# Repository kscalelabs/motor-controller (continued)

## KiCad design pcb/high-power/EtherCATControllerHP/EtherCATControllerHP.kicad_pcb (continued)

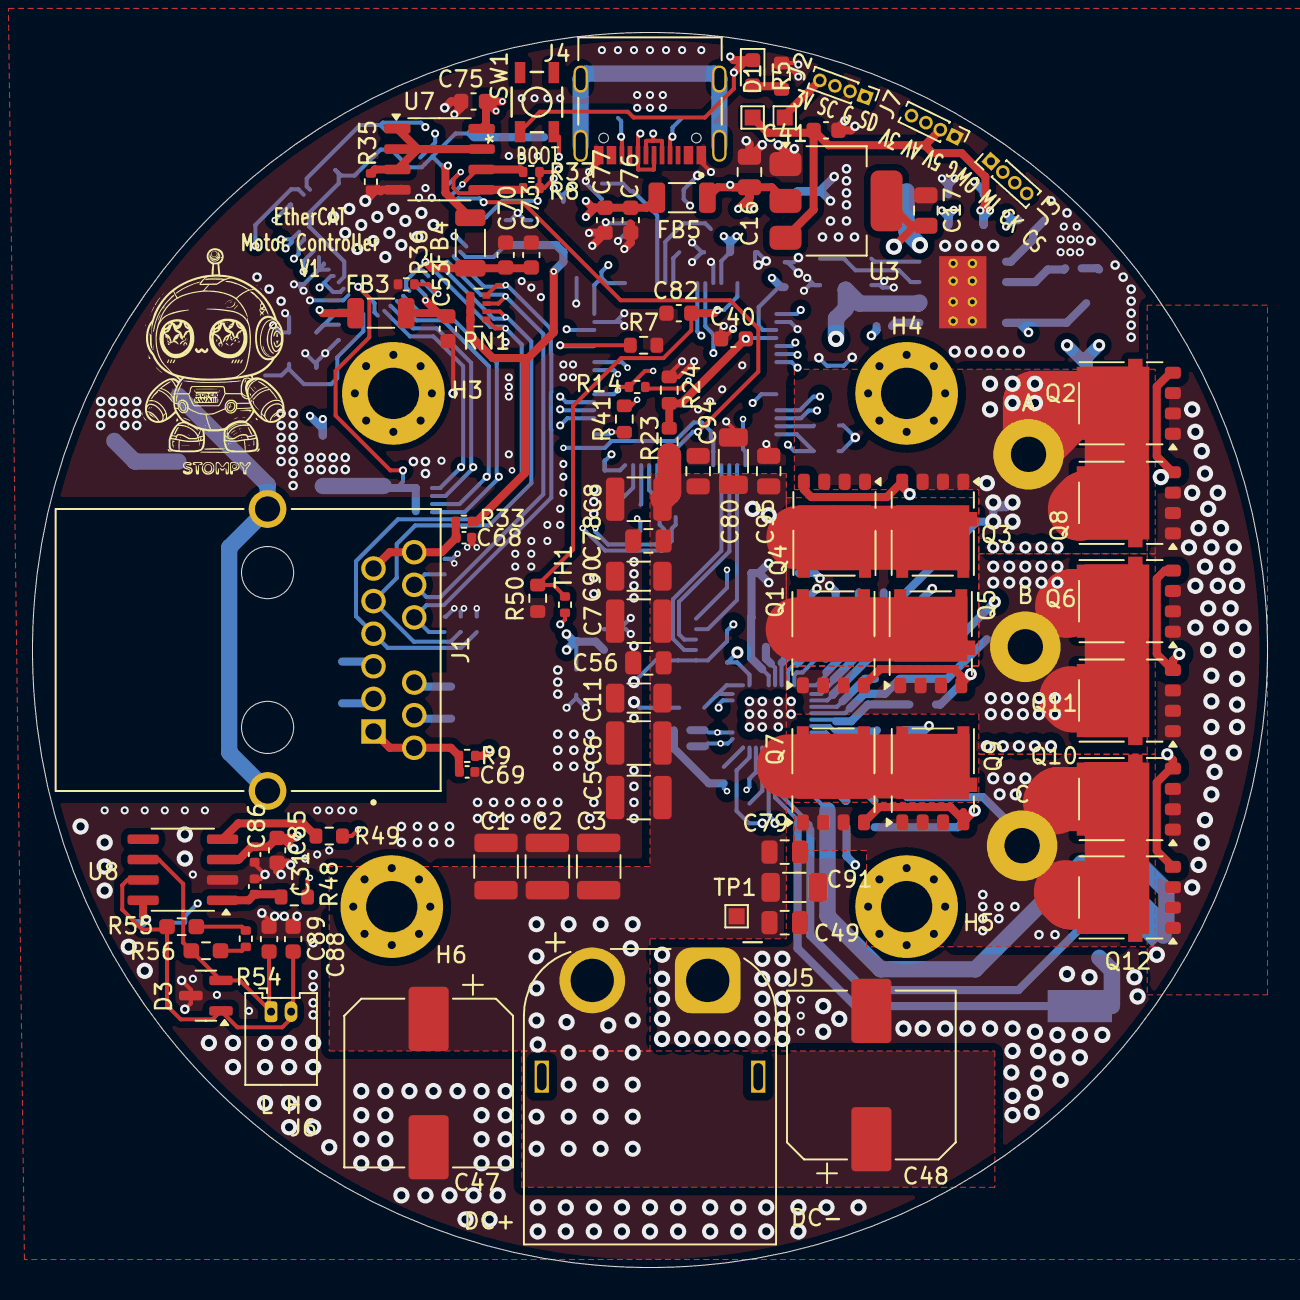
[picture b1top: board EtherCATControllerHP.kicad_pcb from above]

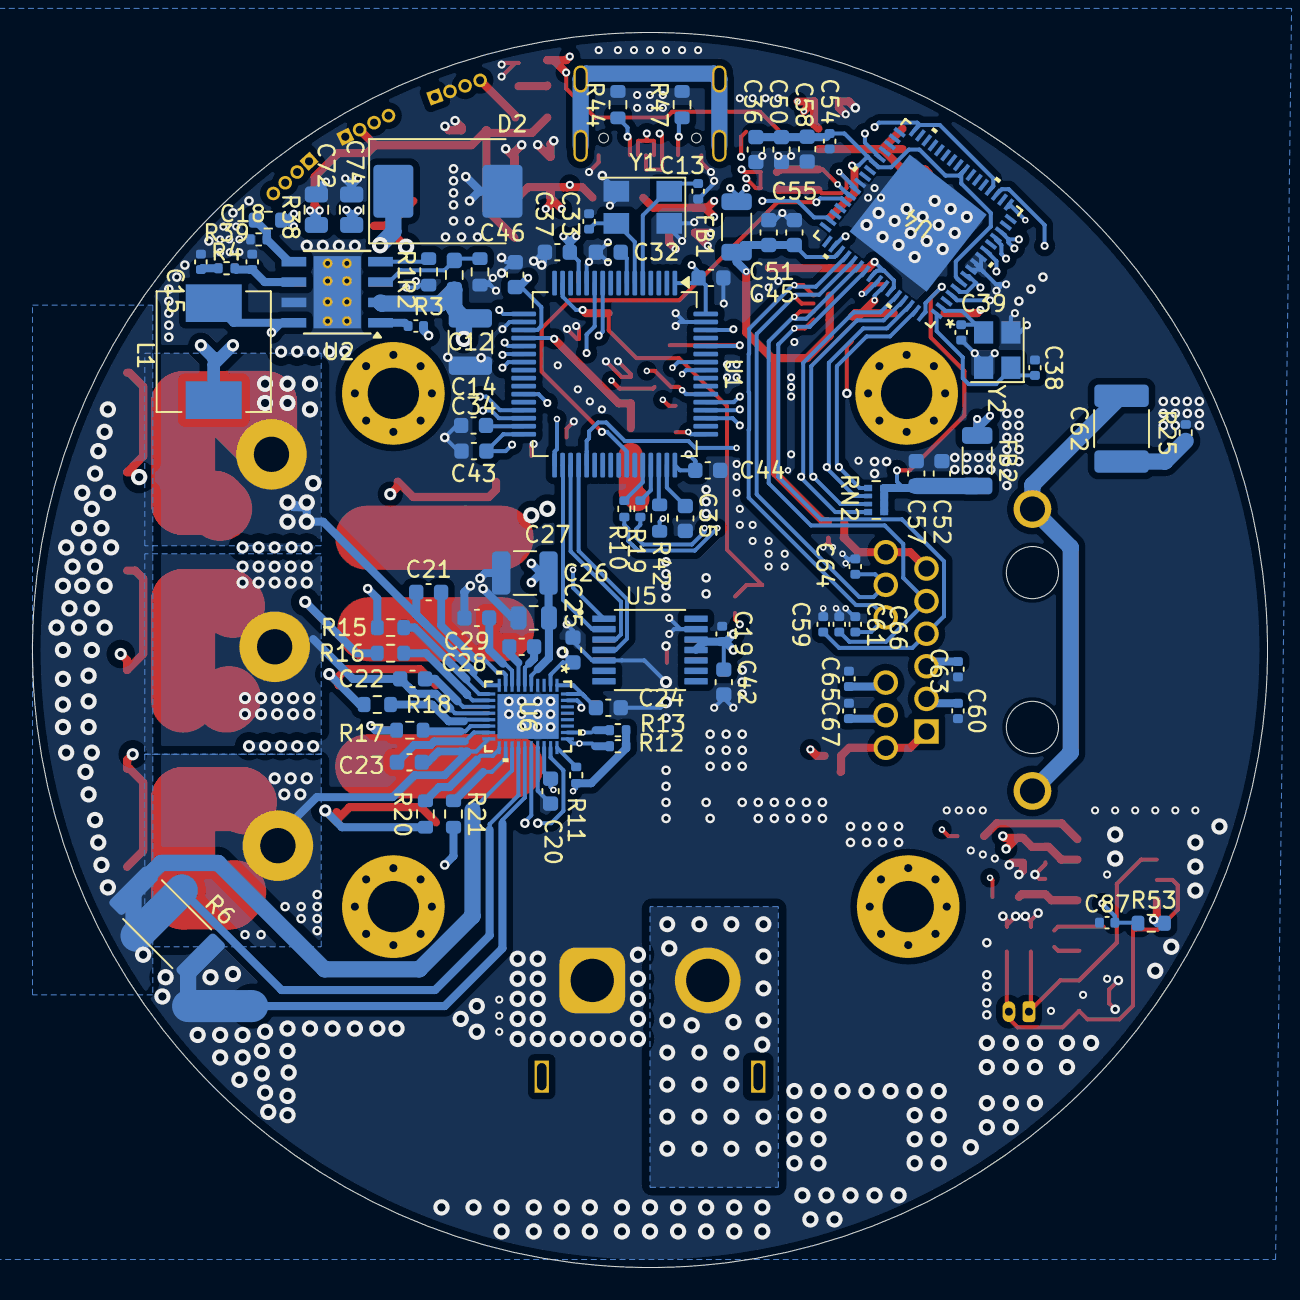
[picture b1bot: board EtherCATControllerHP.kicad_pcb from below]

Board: 6 copper layers, 77.0 x 77.0 mm, 180 parts (85 on the bottom side), 110 nets.

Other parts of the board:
A: SH_A; MountingHole_2.2mm_M2_Pad
B: SH_B; MountingHole_2.2mm_M2_Pad
C: SH_C; MountingHole_2.2mm_M2_Pad
C47: 100uF, 80V; CP_Elec_10x10

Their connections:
/SH_A: A.1; also elsewhere on the board
/SH_B: B.1; also elsewhere on the board
/SH_C: C.1; also elsewhere on the board
DCBUS: C47.1; also elsewhere on the board
GND: C47.2; also elsewhere on the board

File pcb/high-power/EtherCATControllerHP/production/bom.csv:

Designator,Footprint,Quantity,Value,LCSC Part #
"C1, C2, C27, C3, C5, C6, C7, C8",1210,8,10uF, C5156756
"C11, C80, C90, C91",1206,4,1uF,C13832
C12,1210,1,4.7uF,C6120033
"C13, C33, C59, C60, C61, C63, C64, C65, C66, C67",0402,10,10pF,C115606
C14,0402,1,0.1uF, C105883
C15,0402,1,6800pF,C93654
"C16, C17",0805,2,4.7uF,C913498
C18,0402,1,39pF,C147447
C19,0402,1,0.1uF,C77055
"C20, C24, C25, C36, C85",0603,5,1uF,C106858
"C21, C22, C23",0603,3,1uF,C105174
"C26, C49, C56, C78, C79, C94, C95",0805,7,0.1uF,C28233
C28,0603,1,470pF, C107062
C29,0603,1,10uF,C194427
"C31, C86, C87",0402,3,330pF,C526998
"C32, C37, C43, C44, C45, C46, C50, C53, C55, C57, C58, C70, C73, C75, C77, C88, C89",0603,17,0.1uF,C77055
"C34, C35",0603,2,2.2µF,C77183
"C38, C39",0402,2,18pF,C76701
"C40, C41, C82",0603,3,2.2uF,C77183
C42,0603,1,0.1uF,C14663
"C47, C48",CP_Elec_10x10,2,"100uF, 80V", C487410
"C51, C52, C76",0603,3,1uF, C106858
C54,0402,1,470pF,C106207
C62,1812,1,10nF, C574051
"C68, C69",0402,2,0.022uF,C147616
"C72, C74",0805,2,47uF,C178332
D1,0603,1,LTST-C190KGKT,C125094
D2,D_SMC,1,B560C,C85100
D3,SOT-23,1,SM24CANB-02HTG,C2937019
"FB1, FB2, FB3, FB4, FB5",1206,5,"2A, 0.05DCR",C380287
J4,HRO_TYPE-C-31-M-12,1,TYPE-C-31-M-12,C165948
J5,AMASS_XT60PW-M_1x02_P7.20mm_Horizontal,1,XT60PW-M,C98732
J6,Molex_PicoBlade_53048-0210_1x02_P1.25mm_Horizontal,1,2 pin Molex Picoblade,C505099
L1,L_Sunlord_MWSA0603S,1,8.2uH,C408450
"Q1, Q10, Q11, Q12, Q2, Q3, Q4, Q5, Q6, Q7, Q8, Q9",ONSemi_SO-8FL_488AA,12,~,C348543
R1,0603,1,162K, C227450
"R10, R19",0402,2,22R,C107701
"R11, R12, R13, R14",0402,4,5.1K, C105872
"R15, R16, R17, R18, R20, R21",0603,6,2.2R,C112307
R2,0603,1,523K,C23076
R23,0603,1,18K, C98220
"R24, R5",0603,2,1k,C22548
R25,0402,1,1M, C279988
R3,0603,1,84.5k,C706195
"R33, R9",0402,2,0,C106231
R35,0402,1,4.7k, C105871
R36,0402,1,12.1K, C281773
"R37, R8",0402,2,2k,C144035 
R38,0603,1,53.6K,C177851
R39,0402,1,10.2K,C321256
R4,0402,1,13K,C310197
"R41, R42, R48, R49, R53",0603,5,22R,C107701
"R44, R47",0603,2,5.1k, C706184
R50,0603,1,3.3k, C108078
R54,0402,1,120R,C114640
R6,2512,1,500uOhm,C500733 
R7,0603,1,47K,C105579
"RN1, RN2",R_Array_Convex_4x0402,2,49R9, C136850
SW1,SW_EVP-AA102K_PAN,1,EVP-AA202K,C79147
TH1,0402,1,10k,C77131
U1,LQFP-64_10x10mm_P0.5mm,1,STM32F405RGT6,C15742
U2,TI_SO-PowerPAD-8_ThermalVias,1,TPS54360DDAR,C524806
U3,SOT-223,1,LDL1117S33R,C435835
U4,QFN64_ML_MCH,1,LAN9252I/ML,C2758355
U5,SOP65P640X120-14N,1,AS5047P-ATSM,C962063
U6,WQFN36_REE_TEX,1,MCF8329A1IREER,C22399784
U7,SOP-8_3.9x4.9mm_P1.27mm,1,24FC512-I/SN,C615159
U8,SOIC-8_3.9x4.9mm_P1.27mm,1,SN65HVD231,C129257
Y1,Crystal_SMD_5032-4Pin_5.0x3.2mm,1,ABM3B-8.000MHZ-10-1-U-T, C276420
Y2,Crystal_SMD_3225-4Pin_3.2x2.5mm,1,ABM8-25.000MHZ-D2Y-T,C179643

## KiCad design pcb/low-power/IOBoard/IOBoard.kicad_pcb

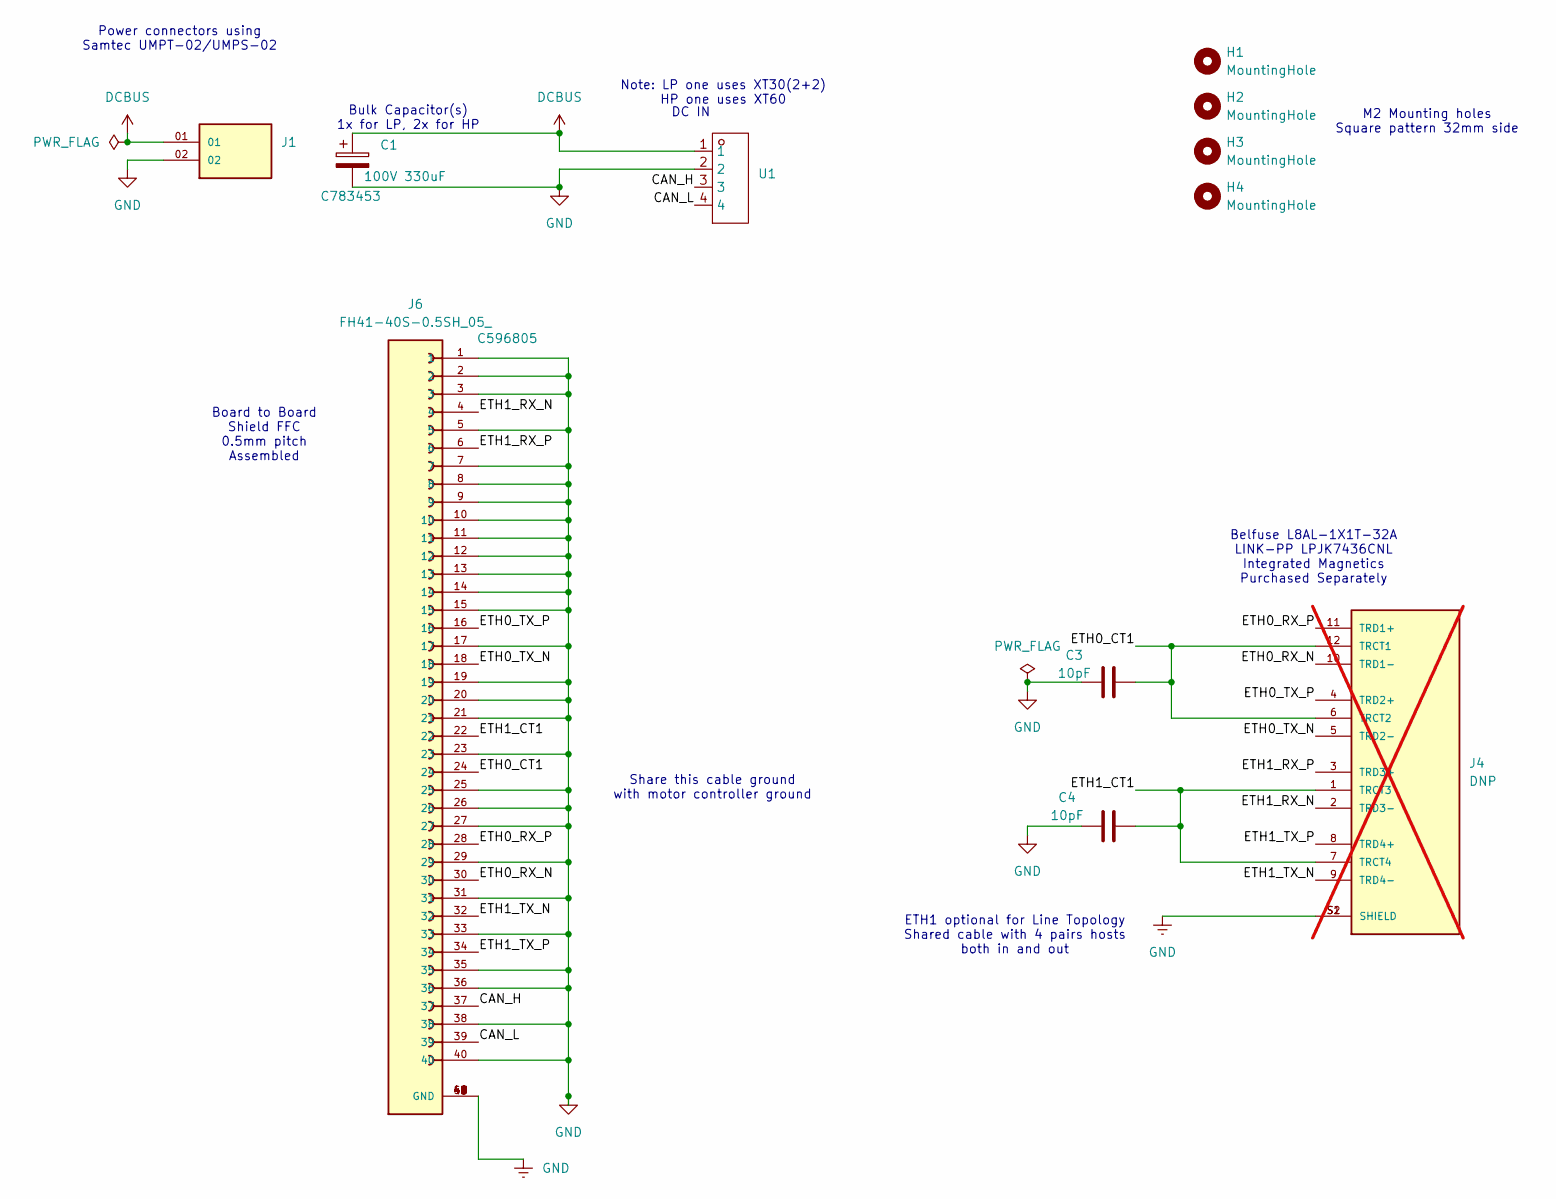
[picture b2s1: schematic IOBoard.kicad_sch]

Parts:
C1: 100V 330uF; CP_Radial_D13.0mm_P5.00mm-Horizontal; LCSC Part # C783453
C3, C4: 10pF; C_0402_1005Metric; LCSC Part # C650948
H1, H2, H3, H4: MountingHole; MountingHole_2.2mm_M2
J1: UMPS-02-03.5-G-V-S-W-TR; SAMTEC_UMPS-02-03.5-G-V-S-W-TR; PARTREV F
J4: DNP; BEL_L8AL-1X1T-32A; PARTREV A; not fitted
J6: FH41-40S-0.5SH_05_; HRS_FH41-40S-0.5SH_05_; PARTREV 18.03.19; LCSC Part # C596805
U1: CONN-TH_4P-XT30PW-M; Manufacturer Part XT30(2+2)PW-M.G.B; LCSC Part Name XT30PW(2+2)功率数据混合插头公金黑PCB弯插

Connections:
/CAN_H: J6.37, U1.3
/CAN_L: J6.39, U1.4
/ETH0_CT1: C3.2, J4.6 (TRCT2), J4.12 (TRCT1), J6.24
/ETH0_RX_N: J4.10 (TRD1-), J6.30
/ETH0_RX_P: J4.11 (TRD1+), J6.28
/ETH0_TX_N: J4.5 (TRD2-), J6.18
/ETH0_TX_P: J4.4 (TRD2+), J6.16
/ETH1_CT1: C4.2, J4.1 (TRCT3), J4.7 (TRCT4), J6.22
/ETH1_RX_N: J4.2 (TRD3-), J6.4
/ETH1_RX_P: J4.3 (TRD3+), J6.6
/ETH1_TX_N: J4.9 (TRD4-), J6.32
/ETH1_TX_P: J4.8 (TRD4+), J6.34
DCBUS: C1.1, J1.01, U1.1
GND: C1.2, C3.1, C4.1, J1.02, J4.S1 (SHIELD), J4.S2 (SHIELD), J6.1, J6.2, J6.3, J6.5, J6.7, J6.8, J6.9, J6.10, J6.11, J6.12, J6.13, J6.14, J6.15, J6.17, J6.19, J6.20, J6.21, J6.23, J6.25, J6.26, J6.27, J6.29, J6.31, J6.33, J6.35, J6.36, J6.38, J6.40, J6.41 (GND), J6.42 (GND), J6.43 (GND), J6.44 (GND), J6.45 (GND), J6.46 (GND), J6.47 (GND), J6.48 (GND), J6.49 (GND), J6.50 (GND), U1.2

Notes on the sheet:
Belfuse L8AL-1X1T-32A LINK-PP LPJK7436CNL Integrated Magnetics Purchased Separately
ETH1 optional for Line Topology Shared cable with 4 pairs hosts both in and out
M2 Mounting holes Square pattern 32mm side
Board to Board Shield FFC 0.5mm pitch Assembled
Share this cable ground with motor controller ground
DC IN
Power connectors using Samtec UMPT-02/UMPS-02
Note: LP one uses XT30(2+2) HP one uses XT60
Bulk Capacitor(s) 1x for LP, 2x for HP

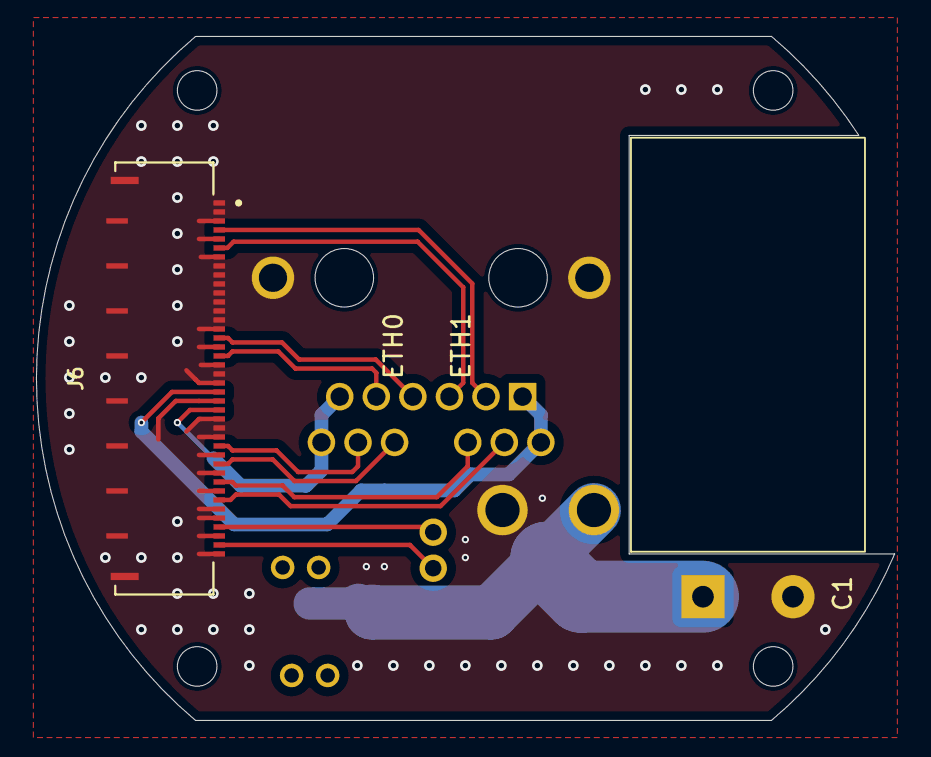
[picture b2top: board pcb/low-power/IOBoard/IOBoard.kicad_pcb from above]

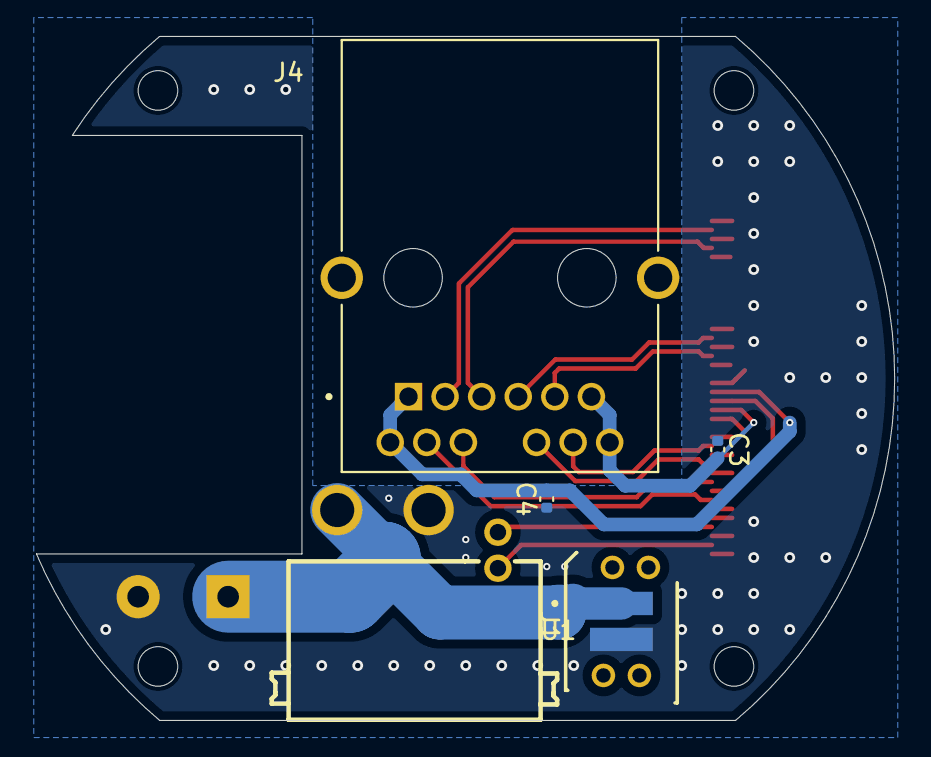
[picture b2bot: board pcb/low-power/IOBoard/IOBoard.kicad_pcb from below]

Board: 2 copper layers, 47.7 x 38.0 mm, 11 parts (5 on the bottom side), 14 nets.

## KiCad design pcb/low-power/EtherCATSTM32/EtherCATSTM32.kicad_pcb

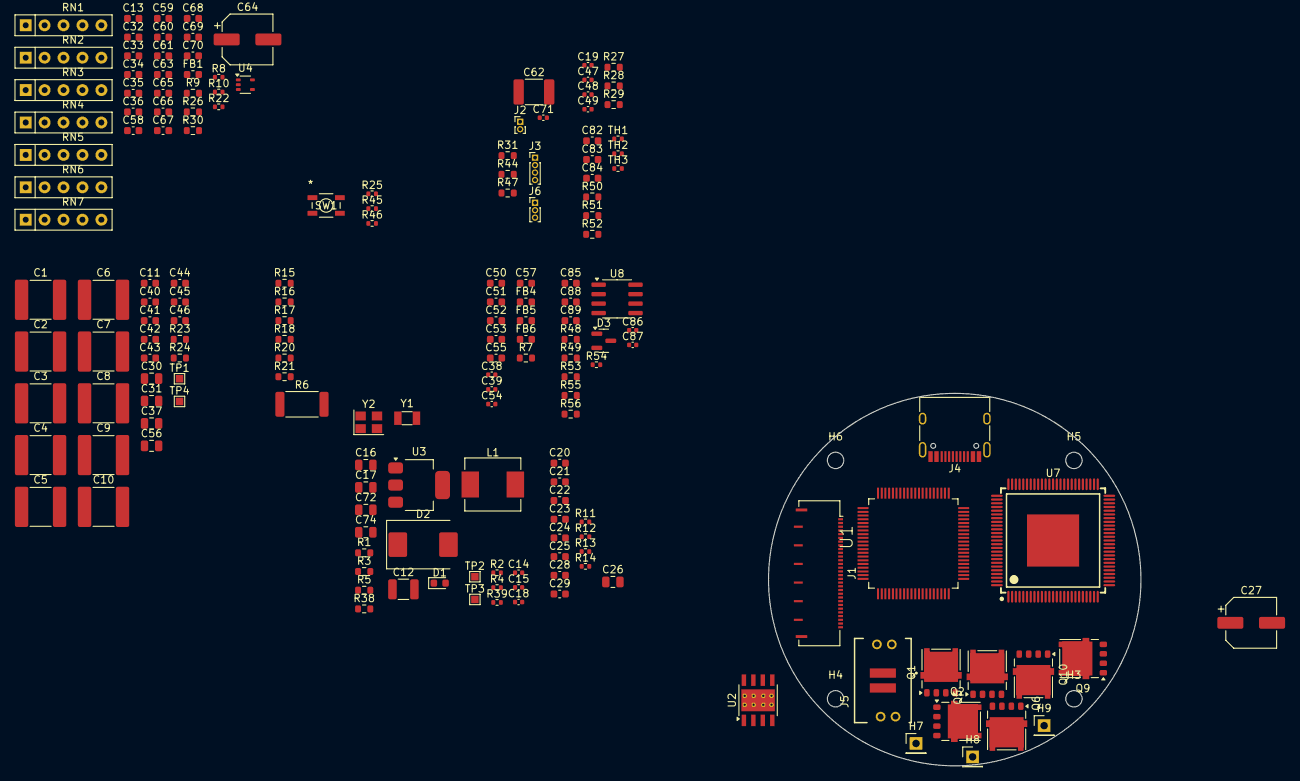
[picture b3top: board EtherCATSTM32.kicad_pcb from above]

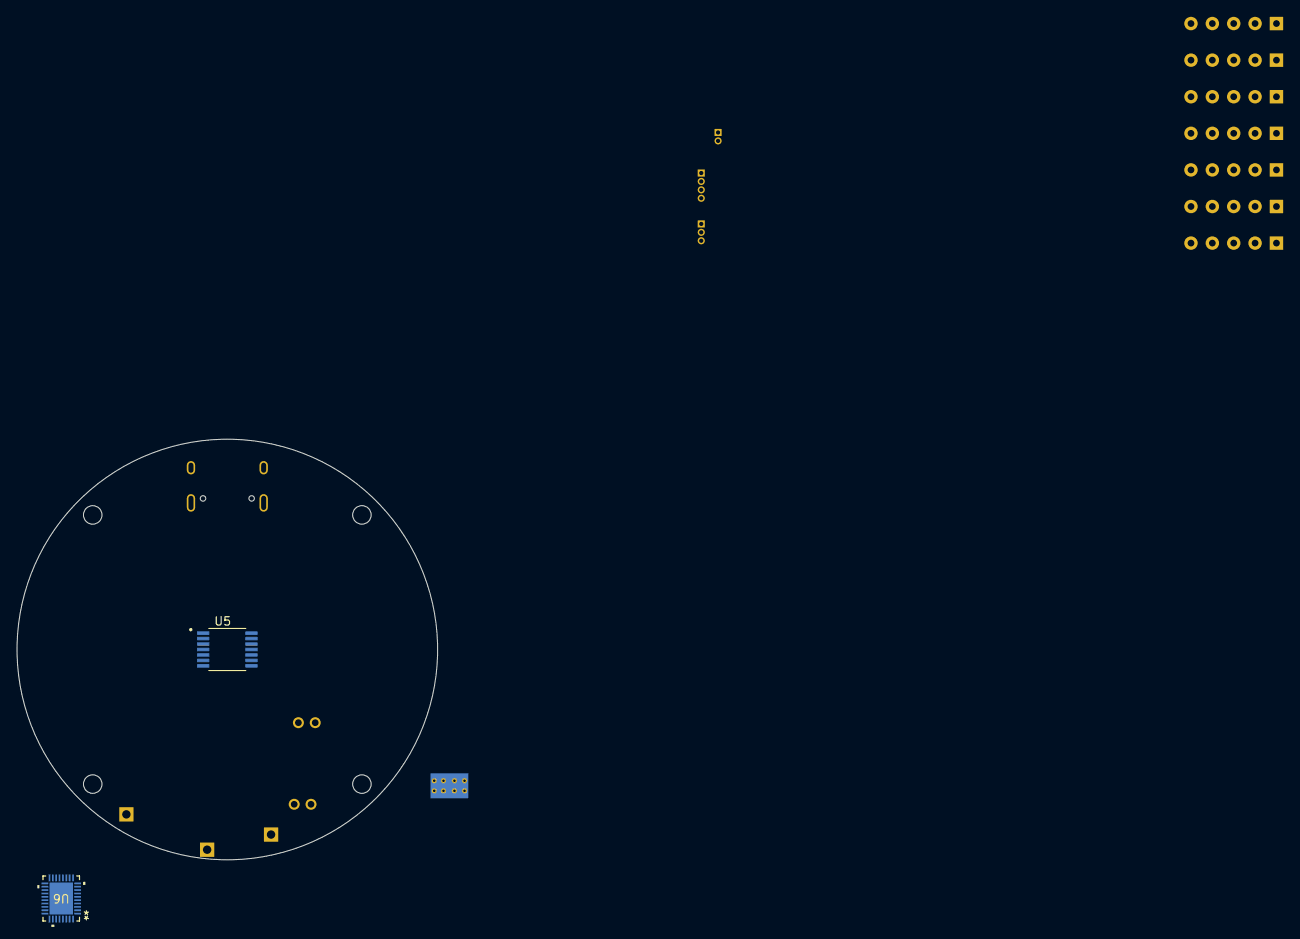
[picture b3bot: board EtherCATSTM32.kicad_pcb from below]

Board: 6 copper layers, 178 parts (2 on the bottom side), 144 nets, no tracks yet.

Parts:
C1, C2, C3, C4, C5, C6, C9, C10: 10uF; C_2220_5750Metric
C7, C8: 22uF; C_2220_5750Metric
C11, C13, C32, C33, C34, C35, C36, C42, C43, C44, C45, C46, C50, C51, C52, C53, C55, C57, C58, C59, C60, C61, C63, C65, C66, C67, C68, C69, C70, C88, C89: 0.1uF; C_0603_1608Metric
C12: 4.7uF; C_1210_3225Metric
C14, C19: 0.1uF; C_0402_1005Metric
C15: 6800pF; C_0402_1005Metric
C16, C17: 4.7uF; C_0805_2012Metric
C18: 39pF; C_0402_1005Metric
C20, C21, C22, C23, C24, C25, C85: 1uF; C_0603_1608Metric
C26: 0.1uF; C_0805_2012Metric
C27, C64: 10uF; CP_Elec_6.3x5.4
C28: 470pF; C_0603_1608Metric
C29: 10uF; C_0603_1608Metric
C30, C31, C37, C56: 10uF; C_0805_2012Metric
C38, C39: 15pF; C_0402_1005Metric
C40, C41, C82, C83, C84: 2.2uF; C_0603_1608Metric
C47, C48, C49: 22nF; C_0402_1005Metric
C54: 10uF; C_0402_1005Metric
C62: 10nF; C_1812_4532Metric
C71: 10nF; C_0402_1005Metric
C72, C74: 47uF; C_0805_2012Metric
C86, C87: 330pF; C_0402_1005Metric
D1: LTST-C190KGKT; D_0603_1608Metric
D2: B560C; D_SMC
D3: SM24CANB-02HTG; SOT-23
FB1, FB4, FB5, FB6: BLM18PG600; L_0603_1608Metric
H3, H4, H5, H6: MountingHole; MountingHole_2.2mm_M2
H7: SH_A; PinHeader_1x01_P2.54mm_Vertical
H8: SH_B; PinHeader_1x01_P2.54mm_Vertical
H9: SH_C; PinHeader_1x01_P2.54mm_Vertical
J1: FH41-40S-0.5SH_05_; Hirose_FH41-30S-0.5SH_1x30_1MP_1SH_P0.5mm_Horizontal
J2: Conn_01x02_Socket; PinHeader_1x02_P1.00mm_Vertical
J3: Conn_01x04_Socket; PinHeader_1x04_P1.00mm_Vertical
J4: TYPE-C-31-M-12; USB_C_Receptacle_HRO_TYPE-C-31-M-12
J5: Mounting holes; SAMTEC_UMPT-02-12.5-X-V-S-W-X
J6: Conn_01x03_Pin; PinHeader_1x03_P1.00mm_Vertical
L1: 8.2uH; L_Sunlord_MWSA0603S
Q1, Q2, Q5, Q6, Q9, Q10: ONSemi_SO-8FL_488AA
R1: 162K; R_0603_1608Metric
R2: 523K; R_0402_1005Metric
R3: 84R5; R_0603_1608Metric
R4: 13K; R_0402_1005Metric
R5, R24: 1k; R_0603_1608Metric
R6: 500uOhm; R_2512_6332Metric
R7: 510R; R_0603_1608Metric
R8: 1.5K; R_0402_1005Metric
R9: 4.87k, 1%; R_0603_1608Metric
R10, R22: 2.2K; R_0402_1005Metric
R11, R12, R13, R14: 5.1K; R_0402_1005Metric
R15, R16, R17, R18, R20, R21: 2.2R; R_0603_1608Metric
R23: 18K; R_0603_1608Metric
R25: 1M; R_0402_1005Metric
R26, R30, R31: 10k; R_0603_1608Metric
R27, R28, R29, R50, R51, R52: 3.3k; R_0603_1608Metric
R38: 53.6K; R_0603_1608Metric
R39: 10.2K; R_0402_1005Metric
R44, R47: 5.1k; R_0603_1608Metric
R45, R46: 22R; R_0402_1005Metric
R48, R49, R53: 22R; R_0603_1608Metric
R54: 120R; R_0402_1005Metric
R55, R56: 0; R_0603_1608Metric
RN1, RN2, RN3, RN4, RN5, RN6, RN7: 49R9; R_Array_SIP5
SW1: EVP-AA202K; SW_EVP-AA102K_PAN
TH1, TH2, TH3: 10k; R_0402_1005Metric
TP1, TP2, TP3, TP4: TESTPOINT; TestPoint_Pad_1.0x1.0mm
U1: DP83849IFVS_NOPB; QFP50P1400X1400X120-80N
U2: TPS54360DDAR; TI_SO-PowerPAD-8_ThermalVias
U3: LDL1117S33R; SOT-223
U4: NC7SZ125P5X; SOT-353_SC-70-5
U5: AS5047P-ATSM; SOP65P640X120-14N
U6: MCF8329A1IREER; WQFN36_REE_TEX
U7: LQFP-100-XMC4800
U8: SN65HVD231; SOIC-8_3.9x4.9mm_P1.27mm
Y1: 32.768 KHZ; Crystal_SMD_3215-2Pin_3.2x1.5mm
Y2: 12 MHz; Crystal_SMD_3225-4Pin_3.2x2.5mm

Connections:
5V: C41.1, C72.1, C74.1, L1.2, R38.1, TP3.1, U3.3 (VIN)
/BRAKE: U6.34 (BRAKE), U7.89 (P0.7)
/CAN_H: C88.1, D3.1 (A1), R55.1, U8.7 (CANH)
/CAN_L: C89.2, D3.2 (A2), R56.2, U8.6 (CANL)
/CAN_MODE: C87.2, R53.1, U7.69 (P1.14)
/CAN_RX: R49.1, U7.70 (P1.13)
/CAN_TX: R48.1, U7.71 (P1.12)
/DIR: U6.31 (DIR), U7.88 (P0.8)
/DRVOFF: U6.24 (DRVOFF), U7.72 (P1.11)
/ECAT0.P0_RXD3: RN3.5 (R4.2), U7.55 (P5.7)
/ECAT0.P0_RXDO: R10.2, U7.58 (P5.0)
/ECAT0.P0_TXD3: RN1.5 (R4.2), U7.77 (P1.2)
/ECAT0.P0_TX_ENA: U1.13 (TX_EN_A), U7.76 (P1.3)
/ECAT0.P1_RXD3: RN4.5 (R4.2), U7.21 (P14.14)
/ECAT0.P1_RX_DVA: U1.62 (RX_DV_B/MII_MODE_B), U7.20 (P14.15)
/ECAT0.P1_RX_ERRB: U1.60 (RX_ER_B/MDIX_EN_B), U7.19 (P15.2)
/ECAT0.P1_TXD1: RN2.5 (R4.2), U7.5 (P3.2)
/ECAT0.P1_TX_ENA: U1.49 (TX_EN_B), U7.7 (P3.0)
/ECAT0.PO_RX_DVA: U1.80 (RX_DV_A/MII_MODE_A), U7.80 (P1.9)
/ECAT0.PO__RX_CLK: RN5.5 (R4.2), U7.78 (P1.1)
/ECAT0_P0_RX_ERRB: U1.2 (RX_ER_A/MDIX_EN_A), U7.54 (P2.6)
/ECAT_RST: R26.1, U4.2 (A), U7.2 (P0.0)
/ETH0_CT1: C69.1, J1.24
/ETH0_RXN: J1.30, U1.23 (TPRDM_A)
/ETH0_RXP: J1.28, RN7.2 (R2.1), U1.24 (TPRDP_A)
/ETH0_TXN: J1.18, RN6.3 (R3.1), U1.26 (TPTDM_A), U1.36 (TPTDM_B)
/ETH0_TXP: J1.16, RN7.5 (R4.2), U1.27 (TPTDP_A)
/ETH1_CT1: C70.1, J1.22
/ETH1_RXN: J1.4, RN6.1 (R1.1), U1.39 (TPRDM_B)
/ETH1_RXP: J1.6, U1.38 (TPRDP_B)
/ETH1_TXP: RN6.4 (R4.1), U1.35 (TPTDP_B)
/ETH_PHY_CLK: U1.70 (X1), U7.85 (P4.0)
/Encoders/ENC_A: C47.1, R27.2
/Encoders/ENC_B: C48.1, R28.2
/Encoders/ENC_Z: C49.1, R29.2
/EtherCAT/COL_PHYAD0_A: R22.1, U1.3 (COL_A)
/EtherCAT/PFBOUT: C58.1, C59.1, C60.1, C61.1, C63.1, C64.1, U1.7 (PFBIN1), U1.28 (PFBIN2), U1.31 (PFBOUT), U1.34 (PFBIN3), U1.54 (PFBIN4)
/EtherCAT/PHY_RST: R30.1, U1.71 (RESET_N), U4.4 (Y)
/EtherCAT/VCCTXRX: C66.1, C67.1, C68.1, FB1.1, RN6.2 (R2.1), RN6.5 (R4.2), RN7.1 (R1.1), RN7.3 (R3.1), RN7.4 (R4.1)
/I2C_SCL: R13.2, U6.30 (SCL), U7.48 (P2.4)
/I2C_SDA: R12.2, U6.29 (SDA), U7.47 (P2.5)
/MCU/RTC_XTAL1: C39.1, U7.16 (RTC_XTAL1), Y1.2
/MCU/RTC_XTAL2: C38.1, U7.15 (RTC_XTAL2), Y1.1
/MCU/VAREF: C57.1, FB5.1, U7.33 (VAREF)
/MCU/VDDA: C55.1, FB6.1, U7.35 (VDDA)
/MCU/XTAL1: U7.61 (XTAL1), Y2.1
/MCU/XTAL2: R7.2, U7.62 (XTAL2)
/MDC: U1.67 (MDC), U7.93 (P3.3)
/MDIO: R8.2, U1.66 (MDIO), U7.94 (P0.12)
/Motor/DVDD: C24.2, U6.1 (DGND), U6.36 (DVDD)
/Motor/GH_A: R15.2, U6.11 (GHA)
/Motor/GH_B: R18.2, U6.15 (GHB)
/Motor/GH_C: R20.2, U6.19 (GHC)
/Motor/GL_A: R16.1, U6.12 (GLA)
/Motor/GL_B: R17.2, U6.16 (GLB)
/Motor/GL_C: R21.1, U6.20 (GLC)
/Motor/SENSE_P: Q2.1 (S), Q2.2 (S), Q2.3 (S), Q6.1 (S), Q6.2 (S), Q6.3 (S), Q10.1 (S), Q10.2 (S), Q10.3 (S), R6.1, U6.21 (LSS), U6.22 (SP)
/NFAULT: R14.2, U6.35 (NFAULT), U7.30 (P14.1)
/POWERDOWN_A: U1.18 (PWRDOWN_INT_A), U7.46 (P2.8)
/POWERDOWN_B: U1.44 (PWRDOWN_INT_B), U7.45 (P2.9)
/Power/Regulators/FB: R38.2, R39.1, U2.5 (FB)
/RESET: C71.1, R31.2, SW1.1, U7.65 (PORST#)
/SH_A: C21.1, H7.1, Q1.1 (S), Q1.2 (S), Q1.3 (S), Q2.5 (D), U6.10 (SHA)
/SH_B: C22.1, H9.1, Q5.1 (S), Q5.2 (S), Q5.3 (S), Q6.5 (D), U6.14 (SHB)
/SH_C: C23.1, H8.1, Q9.1 (S), Q9.2 (S), Q9.3 (S), Q10.5 (D), U6.18 (SHC)
/SPI1_CS: U5.1 (CSN), U7.84 (P4.1)
/SPI1_MISO: U5.3 (MISO), U7.92 (P3.4)
/SPI1_MOSI: U5.4 (MOSI), U7.91 (P3.5)
/SPI1_SCK: U5.2 (CLK), U7.90 (P3.6)
/SPI_CS: J3.1, U7.96 (P0.6)
/SPI_MISO: J3.3, U7.98 (P0.4)
/SPI_MOSI: J3.4, U7.97 (P0.5)
/SPI_SCK: J3.2, U7.95 (P0.11)
/SWV: J6.3, U7.51 (P2.1)
/TCK: J6.2, U7.67 (TCK)
/TEMP_BACKSIDE: C84.1, R52.1, TH3.2, U7.28 (P14.3)
/TEMP_ICS: C83.1, R51.1, TH2.2, U7.27 (P14.4)
/TEMP_MOSFETS: C82.1, R50.1, TH1.2, U7.29 (P14.2)
/TMS: J6.1, U7.66 (TMS)
/UART_RX: J2.2, U7.40 (P2.15)
/UART_TX: J2.1, U7.41 (P2.14)
/USB_D+: J4.A6 (DP1), R46.2, U7.9 (USB_DP)
/USB_D-: J4.A7 (DN1), R45.2, U7.8 (USB_DM)
/VBUS_SENSE: C40.1, R23.2, R24.1, TP4.1, U7.31 (P14.0)
/WAKE: U6.27 (SPEED/_WAKE), U7.73 (P1.10)
AVCC: C19.1, C20.1, C25.2, C42.1, R11.1, R12.1, R13.1, R14.1, R27.1, R28.1, R29.1, TH1.1, TH2.1, TH3.1, U5.11 (VDD), U5.12 (VDD3V3), U6.2 (VREG), U6.26 (AVDD)
DCBUS: C1.1, C2.1, C3.1, C4.1, C5.1, C6.1, C7.1, C8.1, C9.1, C10.1, C12.1, C26.1, C27.1, Q1.5 (D), Q5.5 (D), Q9.5 (D), R2.1, R23.1, TP1.1, U2.2 (VIN), U6.5 (PVDD)
GND: C1.2, C2.2, C3.2, C4.2, C5.2, C6.2, C7.2, C8.2, C9.2, C10.2, C11.2, C12.2, C13.2, C15.2, C16.2, C17.2, C18.2, C19.2, C20.2, C24.1, C25.1, C26.2, C27.2, C29.1, C30.2, C31.2, C32.2, C33.2, C34.2, C35.2, C36.2, C37.2, C38.2, C39.2, C40.2, C41.2, C42.2, C43.2, C44.2, C45.2, C46.2, C47.2, C48.2, C49.2, C50.2, C51.2, C52.2, C53.2, C54.2, C55.2, C56.2, C57.2, C58.2, C59.2, C60.2, C61.2, C63.2, C64.2, C65.2, C66.2, C67.2, C68.2, C69.2, C70.2, C71.2, C72.2, C74.2, C82.2, C83.2, C84.2, C85.1, C86.1, C87.1, C88.2, C89.1, D2.2 (A), D3.3 (common), J1.1, J1.2, J1.3, J1.5, J1.7, J1.8, J1.9, J1.10, J1.11, J1.12, J1.13, J1.14, J1.15, J1.17, J1.19, J1.20, J1.21, J1.23, J1.25, J1.26, J1.27, J1.29, R1.2, R3.2, R5.2, R6.2, R9.1, R22.2, R24.2, R25.2, R26.2, R30.2, R39.2, R44.2, R47.2, R50.2, R51.2, R52.2, SW1.3, U1.6 (COREGND1), U1.10 (IOGND1), U1.22 (ANAGND1), U1.25 (CDGND1), U1.29 (ANAGND2), U1.33 (ANAGND3), U1.37 (CDGND2), U1.40 (ANAGND4), U1.52 (IOGND2), U1.55 (COREGND2), U1.64 (IOGND3), U1.77 (IOGND4), U2.3 (EN), U2.7 (GND), U2.9 (GNDPAD), U3.1 (GND), U4.1 (~OE), U4.3 (GND), U5.5 (TEST), U5.13 (GND), U6.4 (GND), U6.23 (SN), U6.25 (AGND), U6.37 (epad), U7.32 (VAGND), U7.34 (VSSA), U7.59 (VSS), U7.63 (VSSO), U7.101 (EP), U8.2 (GND), Y2.2, Y2.4
unnamed: C15.1, R4.2
unnamed: C62.1, R25.1
unnamed: D1.2, R5.1, TP2.1
unnamed: C14.2, D2.1 (K), L1.1, U2.8 (SW)
unnamed: J4.A5 (CC1), R44.1
unnamed: J4.B5 (CC2), R47.1
unnamed: J4.B7 (DN2), R45.1
unnamed: J4.B6 (DP2), R46.1
unnamed: Q1.4 (G), R15.1
unnamed: Q2.4 (G), R16.2
unnamed: Q5.4 (G), R18.1
unnamed: Q6.4 (G), R17.1
unnamed: Q9.4 (G), R20.1
unnamed: Q10.4 (G), R21.2
unnamed: R2.2, R3.1
unnamed: R7.1, Y2.3
unnamed: R54.1, R56.1
unnamed: R54.2, R55.2
unnamed: RN1.1 (R1.1), U1.14 (TXD0_A)
unnamed: RN1.2 (R2.1), U1.15 (TXD1_A)
unnamed: RN1.3 (R3.1), U1.16 (TXD2_A)
unnamed: RN1.4 (R4.1), U1.17 (TXD3_A/SNI_MODE_A)
unnamed: RN2.1 (R1.1), U1.45 (TXD3_B/SNI_MODE_B)
unnamed: RN2.2 (R2.1), U1.46 (TXD2_B)
unnamed: RN2.3 (R3.1), U1.48 (TXD0_B)
unnamed: RN2.4 (R4.1), U1.47 (TXD1_B)
unnamed: RN3.1 (R1.1), U1.4 (RXD0_A/PHYAD1)
unnamed: RN3.2 (R2.1), U1.5 (RXD1_A/PHYAD2)
unnamed: RN3.3 (R3.1), U1.8 (RXD2_A/CLK2MAC_DIS)
unnamed: RN3.4 (R4.1), U1.9 (RXD3_A/ED_EN_A)
unnamed: RN4.1 (R1.1), U1.58 (RXD0_B/PHYAD3)
unnamed: RN4.2 (R2.1), U1.57 (RXD1_B/PHYAD4)
unnamed: RN4.3 (R3.1), U1.56 (RXD2_B)
unnamed: RN4.4 (R4.1), U1.53 (RXD3_B/ED_EN_B)
unnamed: RN5.1 (R1.1), U1.12 (TX_CLK_A)
unnamed: RN5.2 (R2.1), U1.50 (TX_CLK_B)
unnamed: RN5.3 (R3.1), U1.63 (RX_CLK_B)
unnamed: RN5.4 (R4.1), U1.79 (RX_CLK_A)
unnamed: R9.2, U1.32 (RBIAS)
unnamed: C14.1, U2.1 (BOOT)
unnamed: C18.1, R4.1, U2.6 (COMP)
unnamed: R1.1, U2.4 (RT/CLK)
unnamed: C21.2, U6.9 (BSTA)
unnamed: C22.2, U6.13 (BSTB)
unnamed: C23.2, U6.17 (BSTC)
unnamed: C28.2, U6.7 (CPH)
unnamed: C28.1, U6.6 (CPL)
unnamed: R11.2, U6.28 (FG)
unnamed: C29.2, U6.8 (GVDD)
unnamed: FB4.2, U7.10 (VBUS)
unnamed: R48.2, U8.1 (D)
unnamed: R49.2, U8.4 (R)
unnamed: R53.2, U8.8 (Rs)
SHIELD: C62.2, J4.S1 (SHIELD)
VCC: C11.1, C13.1, C16.1, C17.1, C30.1, C31.1, C32.1, C33.1, C34.1, C35.1, C36.1, C37.1, C43.1, C44.1, C45.1, C46.1, C56.1, C65.1, C85.2, C86.2, D1.1, FB1.2, FB5.2, FB6.2, R8.1, R10.1, R31.1, U1.11 (IOVDD1), U1.30 (ANA33VDD), U1.51 (IOVDD2), U1.65 (IOVDD3), U1.78 (IOVDD4), U3.2 (VOUT), U3.4 (VOUT), U4.5 (VCC), U7.11 (VDDP), U7.12 (VDDC), U7.17 (VBAT), U7.43 (VDDP), U7.60 (VDDP), U7.87 (VDDP), U8.3 (VCC)
VDDC: C50.1, C51.1, C52.1, C53.1, C54.1, U7.42 (VDDC), U7.64 (VDDC), U7.86 (VDDC)

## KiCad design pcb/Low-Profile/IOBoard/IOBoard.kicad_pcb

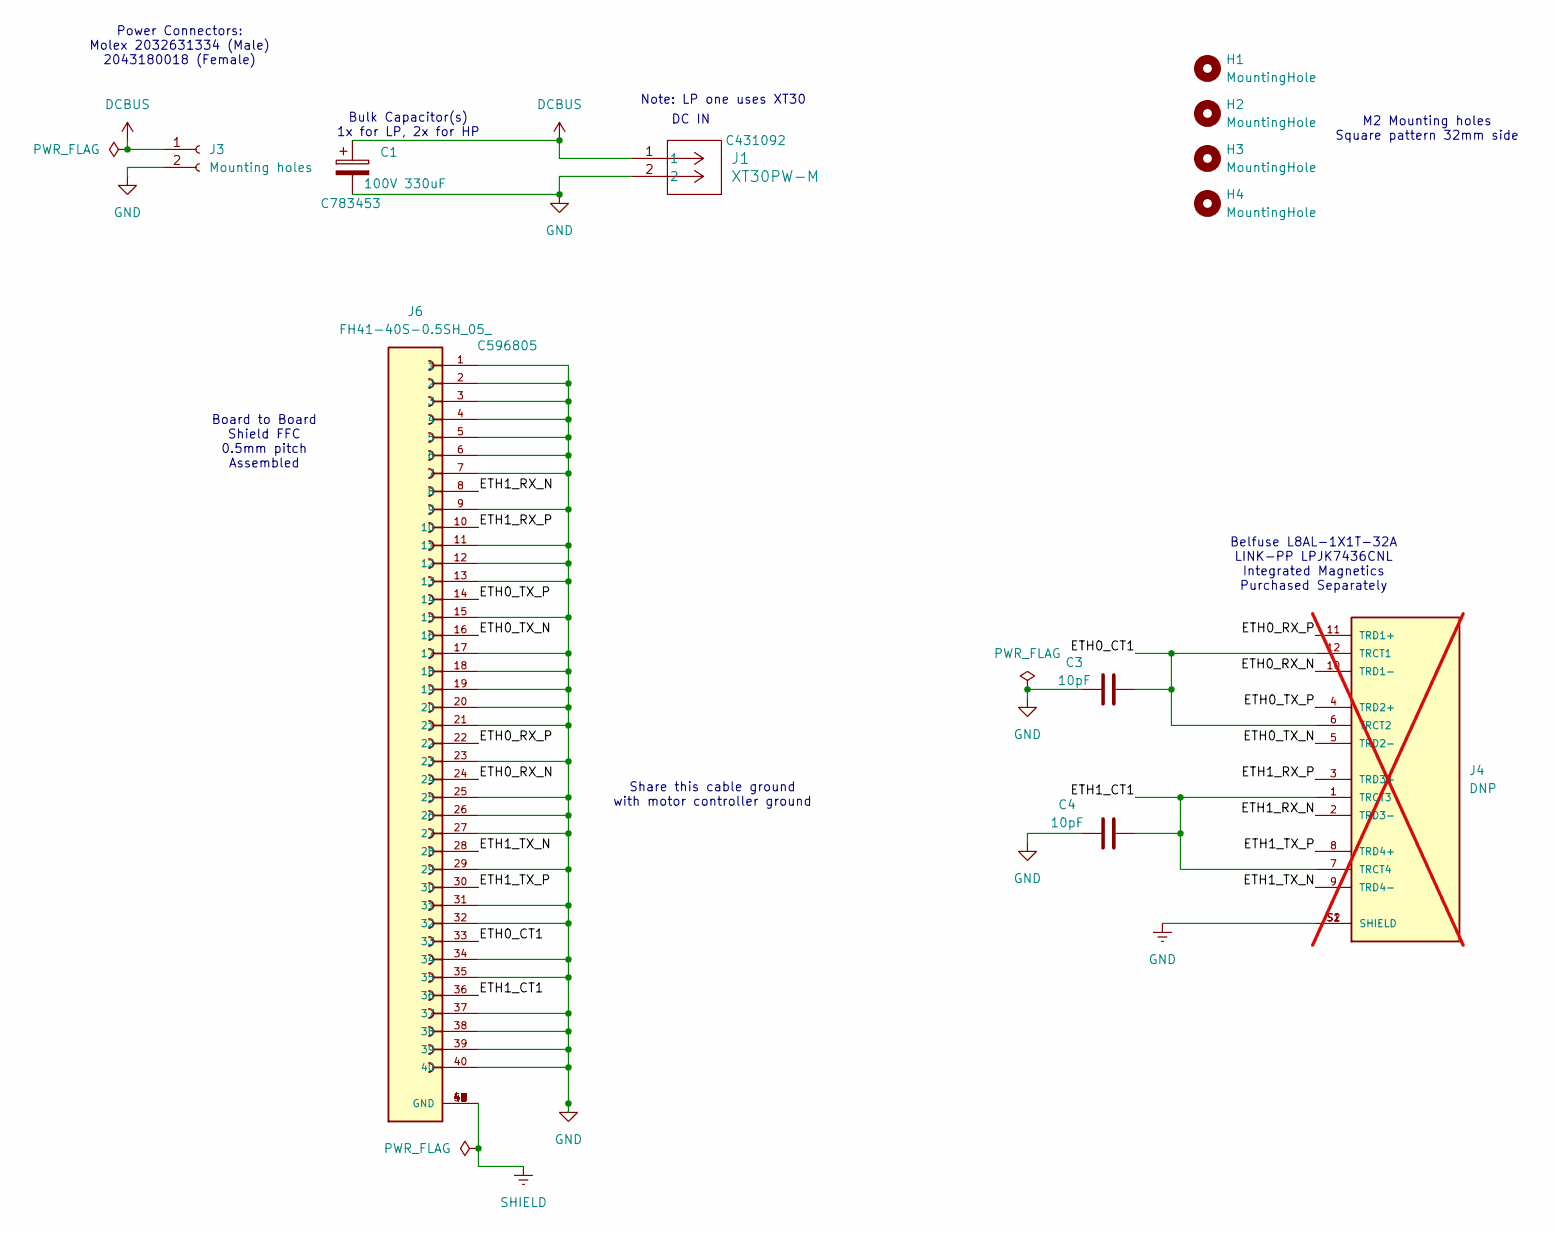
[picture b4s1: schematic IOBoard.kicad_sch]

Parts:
C1: 100V 330uF; CP_Radial_D13.0mm_P5.00mm-Horizontal; LCSC Part # C783453
C3, C4: 10pF; C_0402_1005Metric; LCSC Part # C650948
H1, H2, H3, H4: MountingHole; MountingHole_2.2mm_M2
J1: XT30PW-M; AMASS_XT30PW-M_1x02_P2.50mm_Horizontal; LCSC Part # C431092
J3: Mounting holes; Dual Post
J4: DNP; BEL_L8AL-1X1T-32A; PARTREV A; not fitted
J6: FH41-40S-0.5SH_05_; HRS_FH41-40S-0.5SH_05_; PARTREV 18.03.19; LCSC Part # C596805

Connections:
/ETH0_CT1: C3.2, J4.6 (TRCT2), J4.12 (TRCT1), J6.33
/ETH0_RX_N: J4.10 (TRD1-), J6.24
/ETH0_RX_P: J4.11 (TRD1+), J6.22
/ETH0_TX_N: J4.5 (TRD2-), J6.16
/ETH0_TX_P: J4.4 (TRD2+), J6.14
/ETH1_CT1: C4.2, J4.1 (TRCT3), J4.7 (TRCT4), J6.36
/ETH1_RX_N: J4.2 (TRD3-), J6.8
/ETH1_RX_P: J4.3 (TRD3+), J6.10
/ETH1_TX_N: J4.9 (TRD4-), J6.28
/ETH1_TX_P: J4.8 (TRD4+), J6.30
DCBUS: C1.1, J1.1, J3.1
GND: C1.2, C3.1, C4.1, J1.2, J3.2, J4.S1 (SHIELD), J4.S2 (SHIELD), J6.1, J6.2, J6.3, J6.4, J6.5, J6.6, J6.7, J6.9, J6.11, J6.12, J6.13, J6.15, J6.17, J6.18, J6.19, J6.20, J6.21, J6.23, J6.25, J6.26, J6.27, J6.29, J6.31, J6.32, J6.34, J6.35, J6.37, J6.38, J6.39, J6.40
SHIELD: J6.41 (GND), J6.42 (GND), J6.43 (GND), J6.44 (GND), J6.45 (GND), J6.46 (GND), J6.47 (GND), J6.48 (GND), J6.49 (GND), J6.50 (GND)

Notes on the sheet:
Belfuse L8AL-1X1T-32A LINK-PP LPJK7436CNL Integrated Magnetics Purchased Separately
M2 Mounting holes Square pattern 32mm side
Board to Board Shield FFC 0.5mm pitch Assembled
Share this cable ground with motor controller ground
DC IN
Power Connectors: Molex 2032631334 (Male) 2043180018 (Female)
Note: LP one uses XT30
Bulk Capacitor(s) 1x for LP, 2x for HP

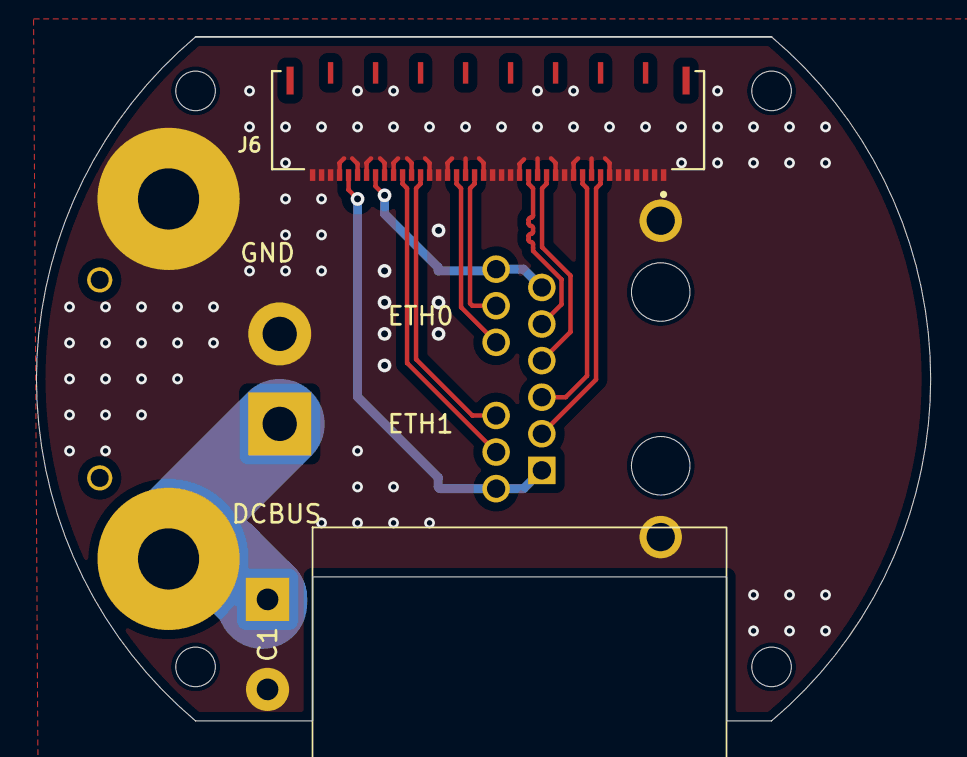
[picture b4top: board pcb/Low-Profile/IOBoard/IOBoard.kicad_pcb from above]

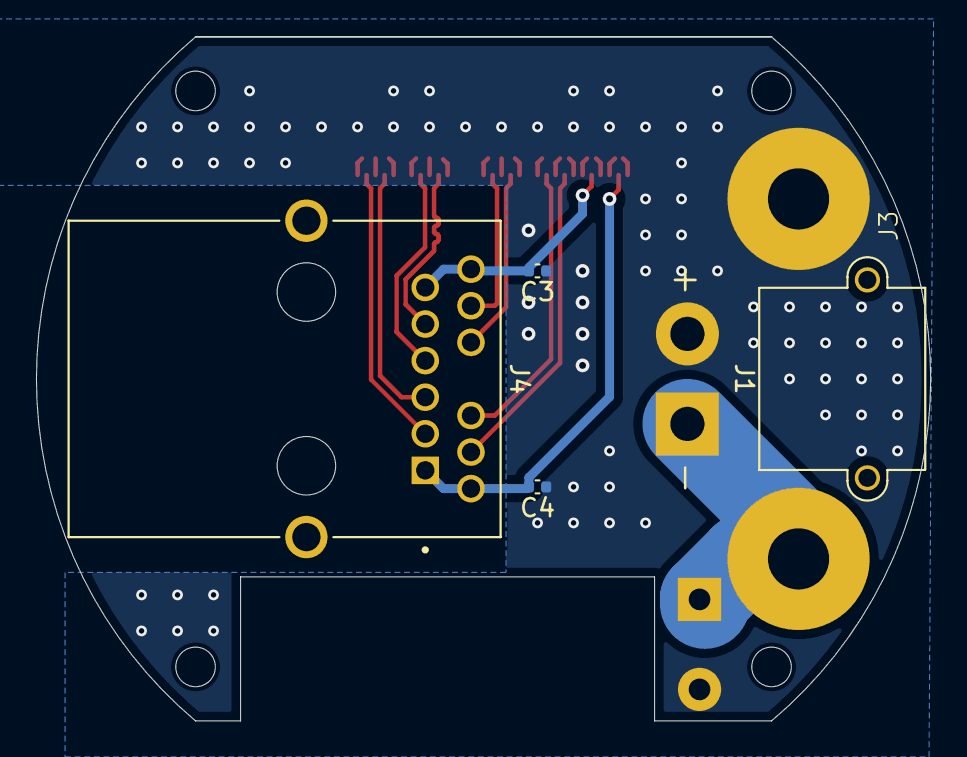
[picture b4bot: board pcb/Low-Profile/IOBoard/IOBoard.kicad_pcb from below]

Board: 2 copper layers, 49.7 x 38.0 mm, 11 parts (5 on the bottom side), 13 nets.

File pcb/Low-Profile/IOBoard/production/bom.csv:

Designator,Footprint,Quantity,Value,LCSC Part #
C1,CP_Radial_D13.0mm_P5.00mm-Horizontal,1,100V 330uF, C783453
"C3, C4",0402,2,10pF, C650948
J1,AMASS_XT30PW-M_1x02_P2.50mm_Horizontal,1,XT30PW-M,C431092
J3,Dual Post,1,Mounting holes,
J6,HRS_FH41-40S-0.5SH_05_,1,FH41-40S-0.5SH_05_,C596805
